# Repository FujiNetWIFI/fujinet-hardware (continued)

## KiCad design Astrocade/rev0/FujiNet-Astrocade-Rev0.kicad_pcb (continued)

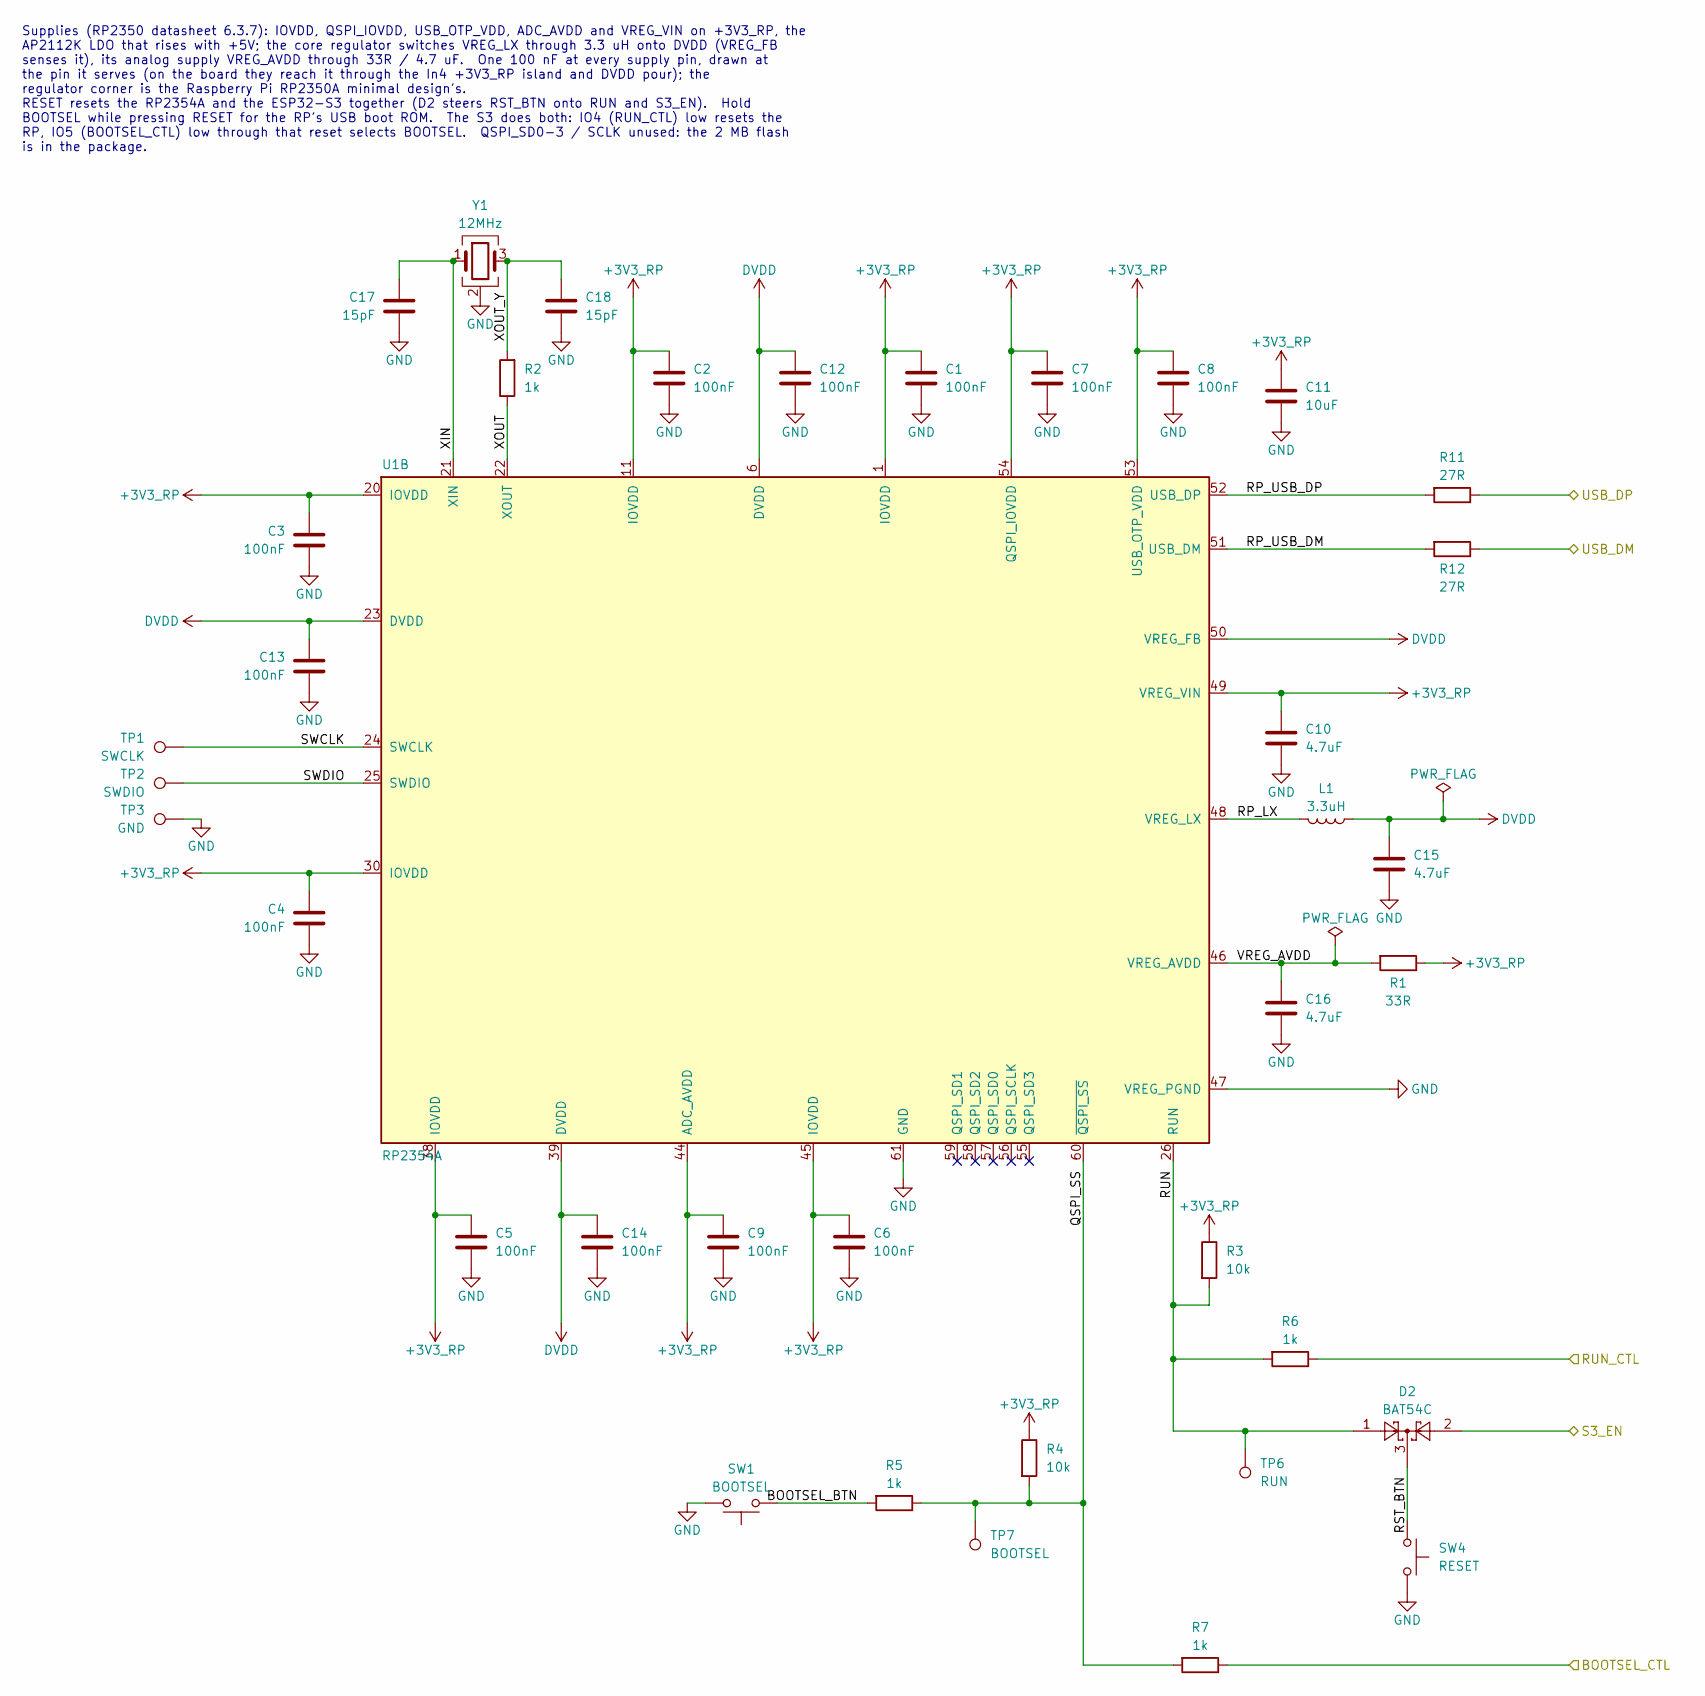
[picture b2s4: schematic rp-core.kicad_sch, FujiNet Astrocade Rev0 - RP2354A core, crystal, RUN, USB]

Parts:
C1, C2, C3, C4, C5, C6, C7, C9, C12, C13, C14: 100nF; C_0603_1608Metric; MPN CC0603KRX7R9BB104; LCSC C14663
C8: 100nF; RPI_C0402; MPN CL05B104KO5NNNC; LCSC C1525
C10, C15: 4.7uF; RPI_C0402_wide; MPN CL05A475MP5NRNC; LCSC C23733
C11: 10uF; C_0603_1608Metric; MPN CL10A106KP8NNNC; LCSC C19702
C16: 4.7uF; RPI_C0402; MPN CL05A475MP5NRNC; LCSC C23733
C17, C18: 15pF; C_0603_1608Metric; MPN CL10C150JB8NNNC; LCSC C1644
D2: BAT54C; SOT-23; MPN BAT54C,215; LCSC C37704
L1: 3.3uH; RPI_L_AOTA-B201610S3R3; MPN AOTA-B201610S3R3-101-T; LCSC C42411119
R1: 33R; RPI_R0402; MPN 0402WGF330JTCE; LCSC C25105
R2, R5, R6, R7: 1k; R_0603_1608Metric; MPN 0603WAF1001T5E; LCSC C21190
R3, R4: 10k; R_0603_1608Metric; MPN 0603WAF1002T5E; LCSC C25804
R11, R12: 27R; RPI_R0402; MPN 0402WGF270JTCE; LCSC C25100
SW1: BOOTSEL; SW_SPST_TL3342; MPN SKQGABE010; LCSC C115351
SW4: RESET; SW_SPST_TL3342; MPN SKQGABE010; LCSC C115351
TP1: SWCLK; TestPoint_Pad_D1.5mm
TP2: SWDIO; TestPoint_Pad_D1.5mm
TP3: GND; TestPoint_Pad_D1.5mm
TP6: RUN; TestPoint_Pad_D1.5mm
TP7: BOOTSEL; TestPoint_Pad_D1.5mm
U1: RP2354A; RPI_RP2350A_QFN60; MPN RP2354A; LCSC C41378174
Y1: 12MHz; Crystal_SMD_3225-4Pin_3.2x2.5mm; MPN ABM8-272-T3; LCSC C20625731

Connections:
+3V3_RP: C1.1, C2.1, C3.1, C4.1, C5.1, C6.1, C7.1, C8.1, C9.1, C10.1, C11.1, R1.1, R3.1, R4.1, U1.1 (IOVDD), U1.11 (IOVDD), U1.20 (IOVDD), U1.30 (IOVDD), U1.38 (IOVDD), U1.44 (ADC_AVDD), U1.45 (IOVDD), U1.49 (VREG_VIN), U1.53 (USB_OTP_VDD), U1.54 (QSPI_IOVDD); also elsewhere on the board
/BOOTSEL_CTL: R7.1; also elsewhere on the board
/RUN_CTL: R6.1; also elsewhere on the board
/S3_EN: D2.2; also elsewhere on the board
/USB_DM: R12.1; also elsewhere on the board
/USB_DP: R11.1; also elsewhere on the board
/rp-core/BOOTSEL_BTN: R5.2, SW1.1
/rp-core/QSPI_SS: R4.2, R5.1, R7.2, TP7.1, U1.60 (~QSPI_SS)
/rp-core/RP_LX: L1.2, U1.48 (VREG_LX)
/rp-core/RP_USB_DM: R12.2, U1.51 (USB_DM)
/rp-core/RP_USB_DP: R11.2, U1.52 (USB_DP)
/rp-core/RST_BTN: D2.3, SW4.1
/rp-core/RUN: D2.1, R3.2, R6.2, TP6.1, U1.26 (RUN)
/rp-core/SWCLK: TP1.1, U1.24 (SWCLK)
/rp-core/SWDIO: TP2.1, U1.25 (SWDIO)
/rp-core/VREG_AVDD: C16.1, R1.2, U1.46 (VREG_AVDD)
/rp-core/XIN: C17.1, U1.21 (XIN), Y1.1
/rp-core/XOUT: R2.1, U1.22 (XOUT)
/rp-core/XOUT_Y: C18.1, R2.2, Y1.3
DVDD: C12.1, C13.1, C14.1, C15.1, L1.1, U1.6 (DVDD), U1.23 (DVDD), U1.39 (DVDD), U1.50 (VREG_FB)
GND: C1.2, C2.2, C3.2, C4.2, C5.2, C6.2, C7.2, C8.2, C9.2, C10.2, C11.2, C12.2, C13.2, C14.2, C15.2, C16.2, C17.2, C18.2, SW1.2, SW4.2, TP3.1, U1.47 (VREG_PGND), U1.61 (GND), Y1.2 (G), Y1.4 (G); also elsewhere on the board

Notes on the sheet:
Supplies (RP2350 datasheet 6.3.7): IOVDD, QSPI_IOVDD, USB_OTP_VDD, ADC_AVDD and VREG_VIN on +3V3_RP, the AP2112K LDO that rises with +5V; the core regulator switches VREG_LX through 3.3 uH onto DVDD (VREG_FB senses it), its analog supply VREG_AVDD through 33R / 4.7 uF. One 100 nF at every supply pi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

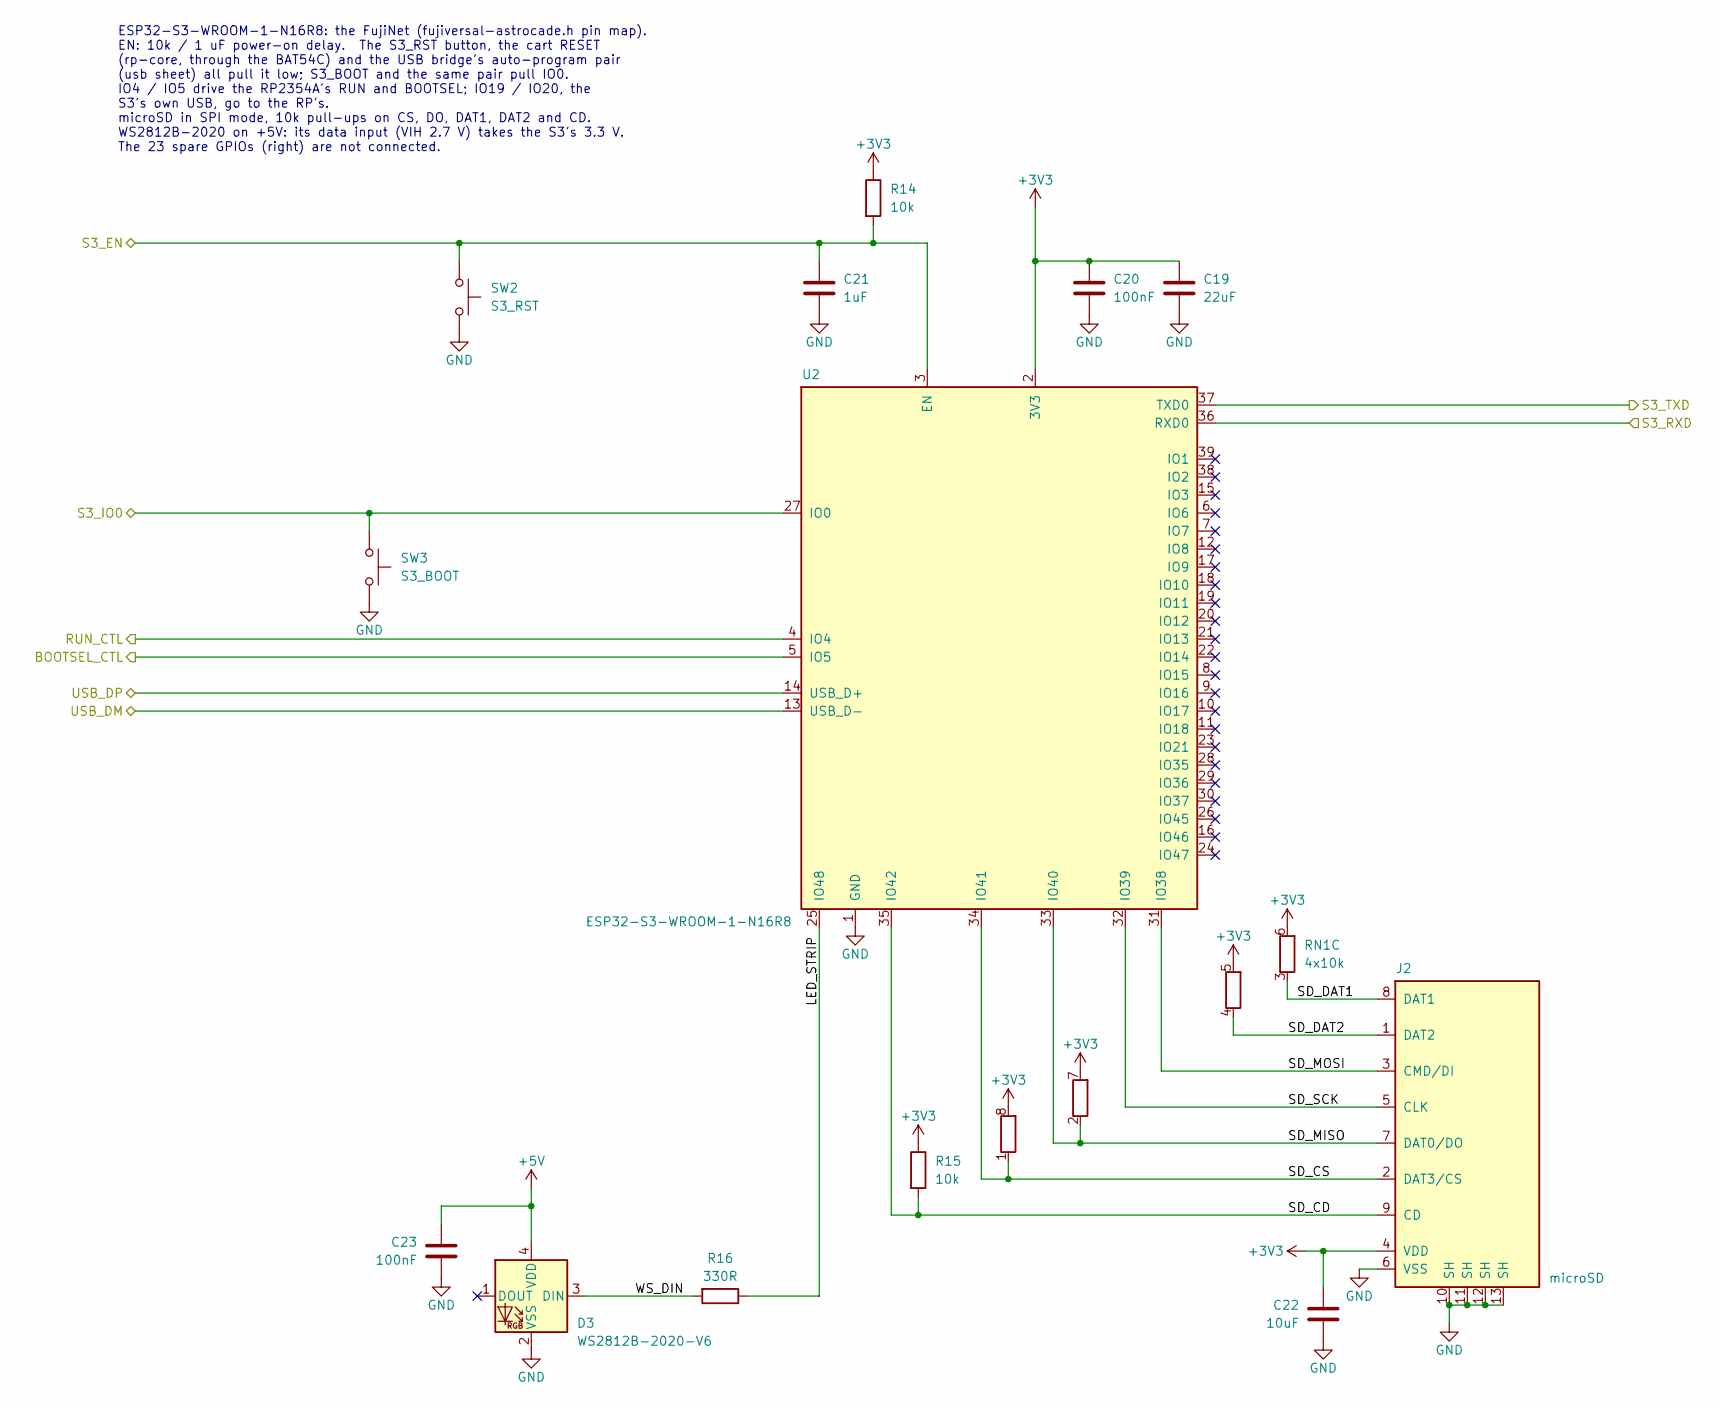
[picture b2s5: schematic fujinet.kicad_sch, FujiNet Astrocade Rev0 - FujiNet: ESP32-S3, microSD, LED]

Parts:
C19: 22uF; C_0805_2012Metric; MPN CL21A226MAQNNNE; LCSC C45783
C20, C23: 100nF; C_0603_1608Metric; MPN CC0603KRX7R9BB104; LCSC C14663
C21: 1uF; C_0603_1608Metric; MPN CL10A105KB8NNNC; LCSC C15849
C22: 10uF; C_0603_1608Metric; MPN CL10A106KP8NNNC; LCSC C19702
D3: WS2812B-2020-V6; LED_WS2812B-2020_PLCC4_2.0x2.0mm; MPN WS2812B-2020-V6; LCSC C52917434
J2: microSD; TF-SMD_TF-015; MPN TF-015; LCSC C113206
R14, R15: 10k; R_0603_1608Metric; MPN 0603WAF1002T5E; LCSC C25804
R16: 330R; R_0603_1608Metric; MPN 0603WAF3300T5E; LCSC C23138
RN1: 4x10k; R_Array_Convex_4x0603; MPN 4D03WGJ0103T5E; LCSC C29718
SW2: S3_RST; SW_SPST_TL3342; MPN TL3342F160QG; LCSC C2886898
SW3: S3_BOOT; SW_SPST_TL3342; MPN TL3342F160QG; LCSC C2886898
U2: ESP32-S3-WROOM-1-N16R8; ESP32-S3-WROOM-1; MPN ESP32-S3-WROOM-1-N16R8; LCSC C2913202

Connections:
+3V3: C19.1, C20.1, C22.1, J2.4 (VDD), R14.1, R15.1, RN1.5 (R4.2), RN1.6 (R3.2), RN1.7 (R2.2), RN1.8 (R1.2), U2.2 (3V3); also elsewhere on the board
+5V: C23.1, D3.4 (VDD); also elsewhere on the board
/BOOTSEL_CTL: U2.5 (IO5); also elsewhere on the board
/RUN_CTL: U2.4 (IO4); also elsewhere on the board
/S3_EN: C21.1, R14.2, SW2.1, U2.3 (EN); also elsewhere on the board
/S3_IO0: SW3.1, U2.27 (IO0); also elsewhere on the board
/S3_RXD: U2.36 (RXD0); also elsewhere on the board
/S3_TXD: U2.37 (TXD0); also elsewhere on the board
/USB_DM: U2.13 (USB_D-); also elsewhere on the board
/USB_DP: U2.14 (USB_D+); also elsewhere on the board
/fujinet/LED_STRIP: R16.1, U2.25 (IO48)
/fujinet/SD_CD: J2.9 (CD), R15.2, U2.35 (IO42)
/fujinet/SD_CS: J2.2 (DAT3/CS), RN1.1 (R1.1), U2.34 (IO41)
/fujinet/SD_DAT1: J2.8 (DAT1), RN1.3 (R3.1)
/fujinet/SD_DAT2: J2.1 (DAT2), RN1.4 (R4.1)
/fujinet/SD_MISO: J2.7 (DAT0/DO), RN1.2 (R2.1), U2.33 (IO40)
/fujinet/SD_MOSI: J2.3 (CMD/DI), U2.31 (IO38)
/fujinet/SD_SCK: J2.5 (CLK), U2.32 (IO39)
/fujinet/WS_DIN: D3.3 (DIN), R16.2
GND: C19.2, C20.2, C21.2, C22.2, C23.2, D3.2 (VSS), J2.6 (VSS), J2.10 (SH), J2.11 (SH), J2.12 (SH), J2.13 (SH), SW2.2, SW3.2, U2.1 (GND), U2.40 (GND), U2.41 (GND); also elsewhere on the board

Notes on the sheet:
ESP32-S3-WROOM-1-N16R8: the FujiNet (fujiversal-astrocade.h pin map). EN: 10k / 1 uF power-on delay. The S3_RST button, the cart RESET (rp-core, through the BAT54C) and the USB bridge's auto-program pair (usb sheet) all pull it low; S3_BOOT and the same pair pull IO0. IO4 / IO5 drive the RP2354A's 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

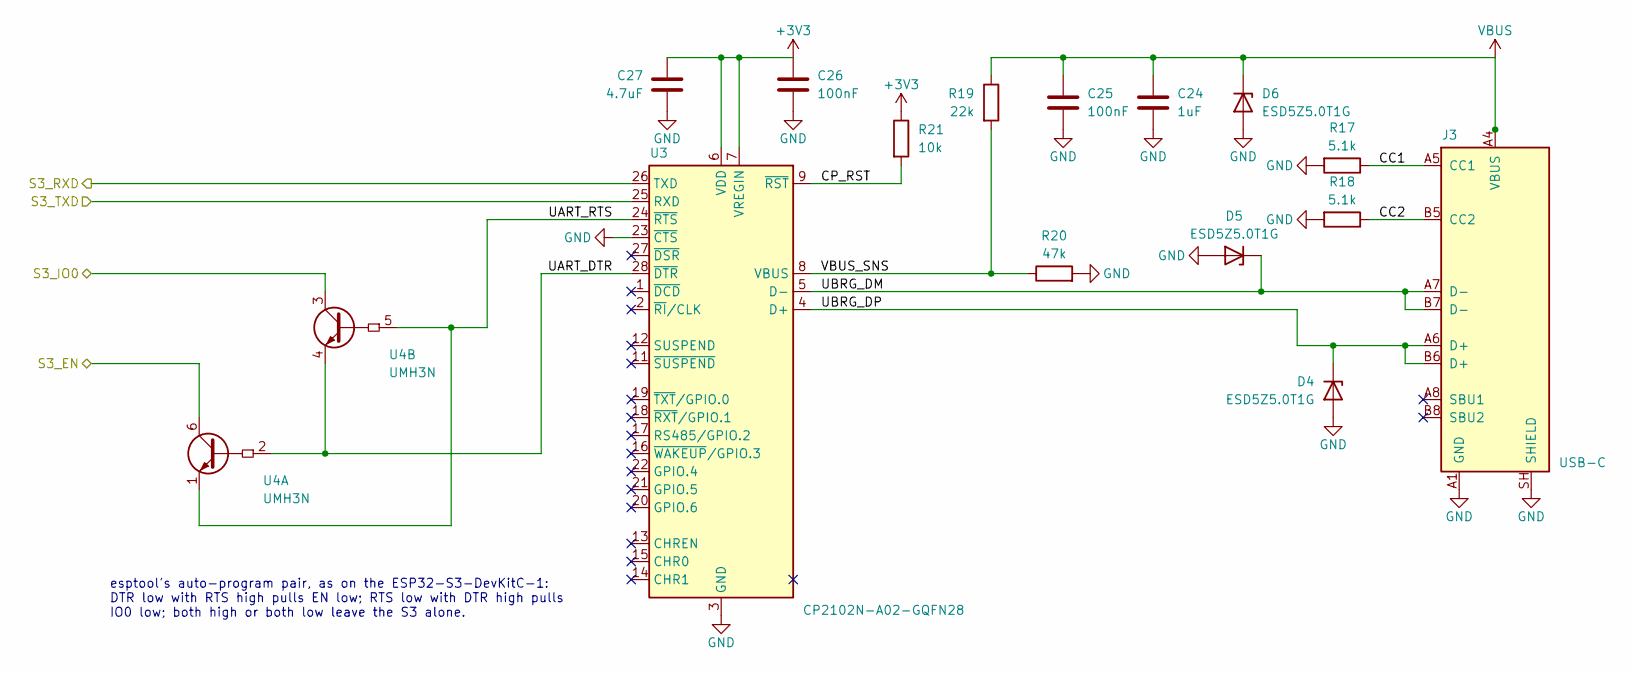
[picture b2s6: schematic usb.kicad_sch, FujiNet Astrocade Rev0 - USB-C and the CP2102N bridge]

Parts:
C24: 1uF; C_0603_1608Metric; MPN CL10A105KB8NNNC; LCSC C15849
C25, C26: 100nF; C_0603_1608Metric; MPN CC0603KRX7R9BB104; LCSC C14663
C27: 4.7uF; C_0603_1608Metric; MPN CL10A475KO8NNNC; LCSC C19666
D4, D5, D6: ESD5Z5.0T1G; D_SOD-523; MPN ESD5Z5.0T1G; LCSC C82044
J3: USB-C; USB_C_Receptacle_HRO_TYPE-C-31-M-12; MPN TYPE-C-31-M-12; LCSC C165948
R17, R18: 5.1k; R_0603_1608Metric; MPN 0603WAF5101T5E; LCSC C23186
R19: 22k; R_0603_1608Metric; MPN 0603WAF2202T5E; LCSC C31850
R20: 47k; R_0603_1608Metric; MPN 0603WAF4702T5E; LCSC C25819
R21: 10k; R_0603_1608Metric; MPN 0603WAF1002T5E; LCSC C25804
U3: CP2102N-A02-GQFN28; QFN-28-1EP_5x5mm_P0.5mm_EP3.35x3.35mm; MPN CP2102N-A02-GQFN28R; LCSC C964632
U4: UMH3N; SOT-363_SC-70-6; MPN UMH3N; LCSC C62892

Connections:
+3V3: C26.1, C27.1, R21.1, U3.6 (VDD), U3.7 (VREGIN); also elsewhere on the board
/S3_EN: U4.6 (C1); also elsewhere on the board
/S3_IO0: U4.3 (C2); also elsewhere on the board
/S3_RXD: U3.26 (TXD); also elsewhere on the board
/S3_TXD: U3.25 (RXD); also elsewhere on the board
/usb/CC1: J3.A5 (CC1), R17.1
/usb/CC2: J3.B5 (CC2), R18.1
/usb/CP_RST: R21.2, U3.9 (~RST)
/usb/UART_DTR: U3.28 (~DTR), U4.2 (B1), U4.4 (E2)
/usb/UART_RTS: U3.24 (~RTS), U4.1 (E1), U4.5 (B2)
/usb/UBRG_DM: D5.1 (K), J3.A7 (D-), J3.B7 (D-), U3.5 (D-)
/usb/UBRG_DP: D4.1 (K), J3.A6 (D+), J3.B6 (D+), U3.4 (D+)
/usb/VBUS_SNS: R19.2, R20.1, U3.8 (VBUS)
GND: C24.2, C25.2, C26.2, C27.2, D4.2 (A), D5.2 (A), D6.2 (A), J3.A1 (GND), J3.A12 (GND), J3.B1 (GND), J3.B12 (GND), J3.SH (SHIELD), R17.2, R18.2, R20.2, U3.3 (GND), U3.23 (~CTS), U3.29 (GND); also elsewhere on the board
VBUS: C24.1, C25.1, D6.1 (K), J3.A4 (VBUS), J3.A9 (VBUS), J3.B4 (VBUS), J3.B9 (VBUS), R19.1; also elsewhere on the board

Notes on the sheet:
esptool's auto-program pair, as on the ESP32-S3-DevKitC-1: DTR low with RTS high pulls EN low; RTS low with DTR high pulls IO0 low; both high or both low leave the S3 alone.

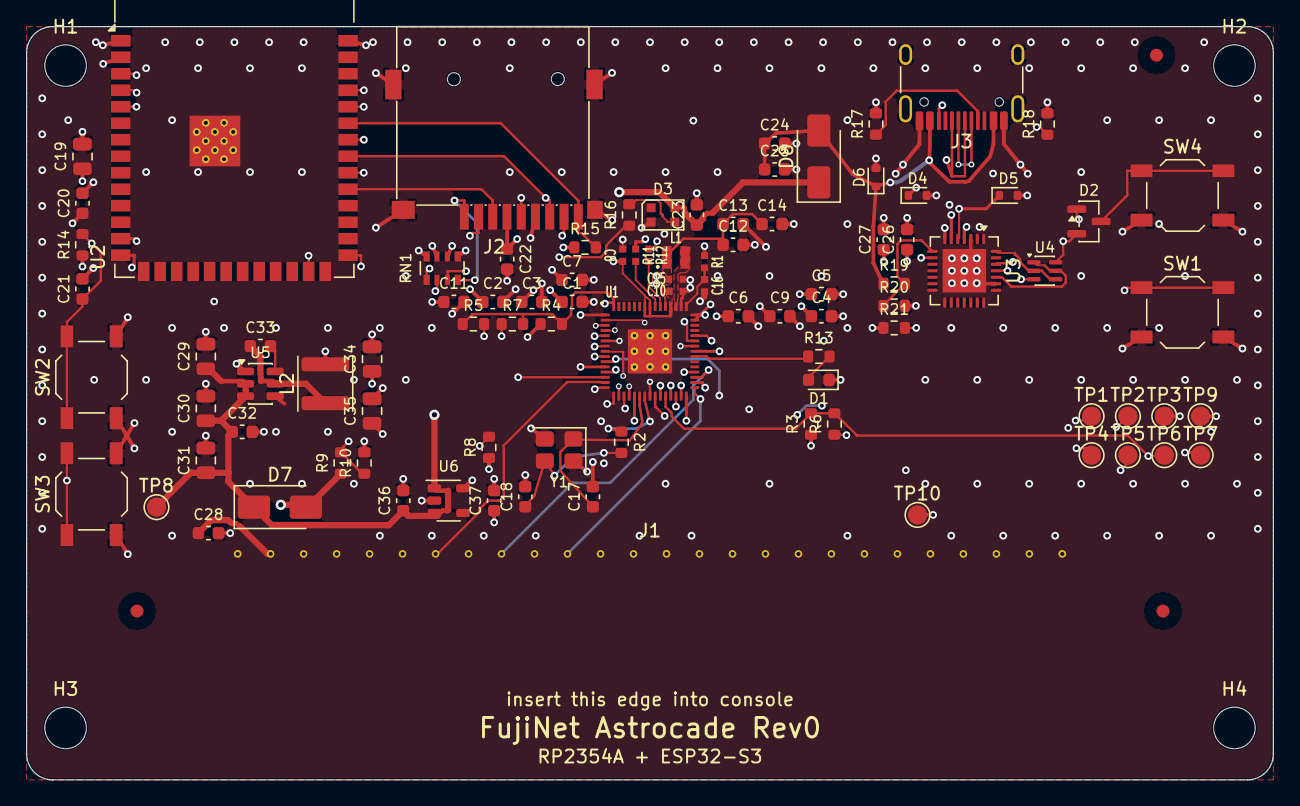
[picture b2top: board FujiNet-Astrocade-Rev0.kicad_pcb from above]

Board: 6 copper layers, 96.0 x 58.0 mm, 100 parts (0 on the bottom side), 74 nets.

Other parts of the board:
FID1, FID2, FID3: Fiducial_1mm_Mask2mm
H1, H2, H3, H4: M3; MountingHole_3.2mm_NPTH

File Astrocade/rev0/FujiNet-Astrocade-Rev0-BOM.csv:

"Refs","Value","Footprint","MPN","LCSC","Description","DNP"
"C1,C2,C3,C4,C5,C6,C7,C9,C12,C13,C14,C20,C23,C25,C26,C28,C32,C33","100nF","C_0603_1608Metric","CC0603KRX7R9BB104","C14663","IOVDD decoupling",""
"C8","100nF","RPI_C0402","CL05B104KO5NNNC","C1525","USB_OTP_VDD + QSPI_IOVDD decoupling",""
"C10,C15","4.7uF","RPI_C0402_wide","CL05A475MP5NRNC","C23733","VREG_VIN bulk",""
"C11,C22","10uF","C_0603_1608Metric","CL10A106KP8NNNC","C19702","RP 3V3 bulk",""
"C16","4.7uF","RPI_C0402","CL05A475MP5NRNC","C23733","VREG_AVDD filter",""
"C17,C18","15pF","C_0603_1608Metric","CL10C150JB8NNNC","C1644","crystal load",""
"C19,C29,C30,C31,C34,C35","22uF","C_0805_2012Metric","CL21A226MAQNNNE","C45783","S3 bulk (WiFi TX bursts)",""
"C21,C24,C36,C37","1uF","C_0603_1608Metric","CL10A105KB8NNNC","C15849","EN power-on delay",""
"C27","4.7uF","C_0603_1608Metric","CL10A475KO8NNNC","C19666","CP2102N VDD bulk",""
"D1","green","LED_0603_1608Metric","KT-0603G","C12624","RP activity LED",""
"D2","BAT54C","SOT-23","BAT54C,215","C37704","RESET steering, common cathode",""
"D3","WS2812B-2020-V6","LED_WS2812B-2020_PLCC4_2.0x2.0mm","WS2812B-2020-V6","C52917434","status LED on +5V (datasheet VDD 3.7-5.3 V; VIH 2.7 V takes 3.3 V data)",""
"D4,D5,D6","ESD5Z5.0T1G","D_SOD-523","ESD5Z5.0T1G","C82044","ESD",""
"D7,D8","SS34","D_SMA","SS34","C8678","console 5V OR-ing",""
"J2","microSD","TF-SMD_TF-015","TF-015","C113206","microSD push-push, SPI mode",""
"J3","USB-C","USB_C_Receptacle_HRO_TYPE-C-31-M-12","TYPE-C-31-M-12","C165948","power + S3 programming",""
"L1","3.3uH","RPI_L_AOTA-B201610S3R3","AOTA-B201610S3R3-101-T","C42411119","RP2350 core SMPS inductor",""
"L2","6.8uH","L_Sunlord_SWPA4030S","SWPA4030S6R8MT","C62684","buck inductor",""
"R1","33R","RPI_R0402","0402WGF330JTCE","C25105","VREG_AVDD filter",""
"R2,R5,R6,R7","1k","R_0603_1608Metric","0603WAF1001T5E","C21190","crystal drive limit",""
"R3,R4,R8,R9,R14,R15,R21","10k","R_0603_1608Metric","0603WAF1002T5E","C25804","RUN pull-up",""
"R10","15k","R_0603_1608Metric","0603WAF1502T5E","C22809","console 5V sense -> 3.0V (6 kOhm: beats RP2350-E9)",""
"R11,R12","27R","RPI_R0402","0402WGF270JTCE","C25100","USB series",""
"R13,R16","330R","R_0603_1608Metric","0603WAF3300T5E","C23138","LED series (KT-0603G VF ~2.6-2.85 V: 1.5-2 mA from 3.3 V)",""
"R17,R18","5.1k","R_0603_1608Metric","0603WAF5101T5E","C23186","UFP Rd",""
"R19","22k","R_0603_1608Metric","0603WAF2202T5E","C31850","VBUS sense divider",""
"R20","47k","R_0603_1608Metric","0603WAF4702T5E","C25819","VBUS sense divider",""
"RN1","4x10k","R_Array_Convex_4x0603","4D03WGJ0103T5E","C29718","SD pull-ups",""
"SW1","BOOTSEL","SW_SPST_TL3342","SKQGABE010","C115351","RP2354 BOOTSEL (hold while pressing RESET)",""
"SW2","S3_RST","SW_SPST_TL3342","SKQGABE010","C115351","ESP32-S3 EN",""
"SW3","S3_BOOT","SW_SPST_TL3342","SKQGABE010","C115351","ESP32-S3 BOOT (IO0)",""
"SW4","RESET","SW_SPST_TL3342","SKQGABE010","C115351","cart RESET: RP RUN + S3 EN via BAT54C",""
"U1","RP2354A","RPI_RP2350A_QFN60","RP2354A","C41378174","RP2350A + 2MB flash in package; cart bus server",""
"U2","ESP32-S3-WROOM-1-N16R8","ESP32-S3-WROOM-1","ESP32-S3-WROOM-1-N16R8","C2913202","FujiNet core (fujiversal-astrocade)",""
"U3","CP2102N-A02-GQFN28","QFN-28-1EP_5x5mm_P0.5mm_EP3.35x3.35mm","CP2102N-A02-GQFN28R","C964632","USB-UART for S3 flashing/console (self-powered)",""
"U4","UMH3N","SOT-363_SC-70-6","UMH3N","C62892","esptool auto-program (DevKitC-1 style)",""
"U5","AP63203WU","TSOT-23-6","AP63203WU-7","C780769","3.3V 2A buck",""
"U6","AP2112K-3.3","SOT-23-5","AP2112K-3.3TRG1","C51118","RP2354A 3.3V LDO (IOVDD, VREG_VIN, VREG_AVDD), fast start",""
"Y1","12MHz","Crystal_SMD_3225-4Pin_3.2x2.5mm","ABM8-272-T3","C20625731","",""

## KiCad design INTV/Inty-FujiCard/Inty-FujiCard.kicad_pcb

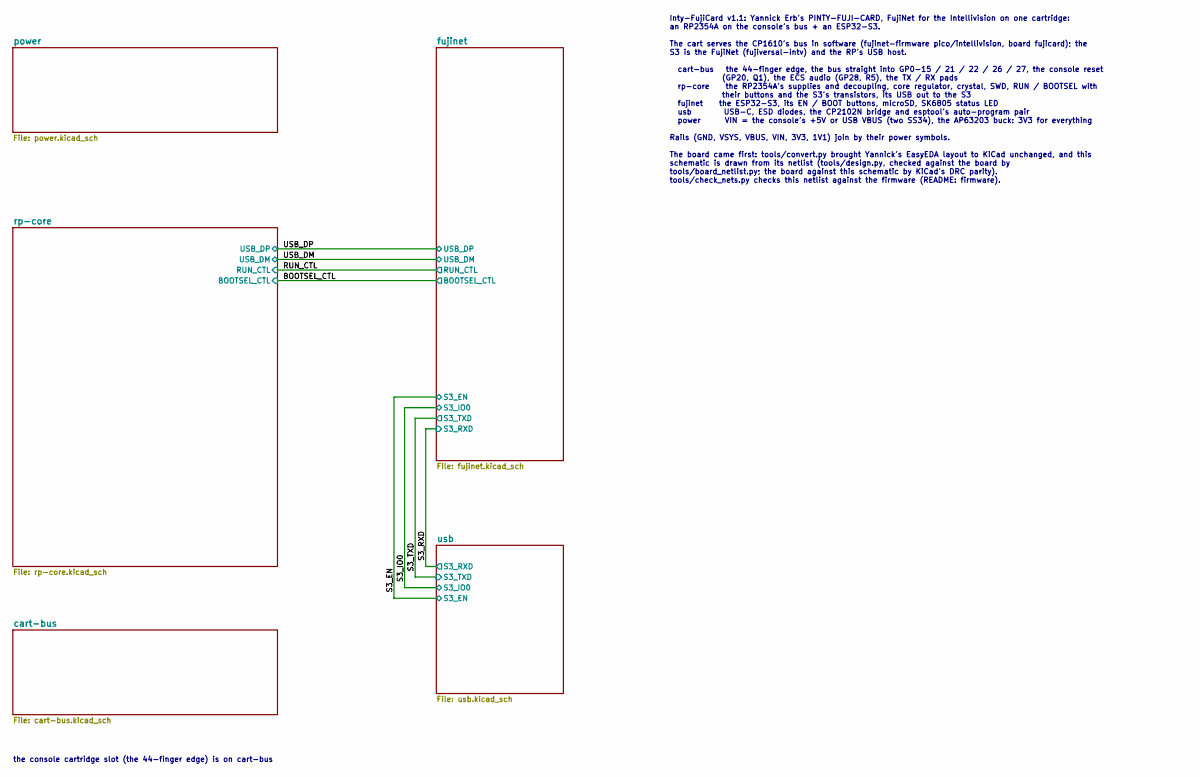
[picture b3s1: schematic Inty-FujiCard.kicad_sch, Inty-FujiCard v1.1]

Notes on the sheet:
the console cartridge slot (the 44-finger edge) is on cart-bus
Inty-FujiCard v1.1: Yannick Erb's PINTY-FUJI-CARD, FujiNet for the Intellivision on one cartridge: an RP2354A on the console's bus + an ESP32-S3. The cart serves the CP1610's bus in software (fujinet-firmware pico/intellivision, board fujicard); the S3 is the FujiNet (fujiversal-intv) and the RP's 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

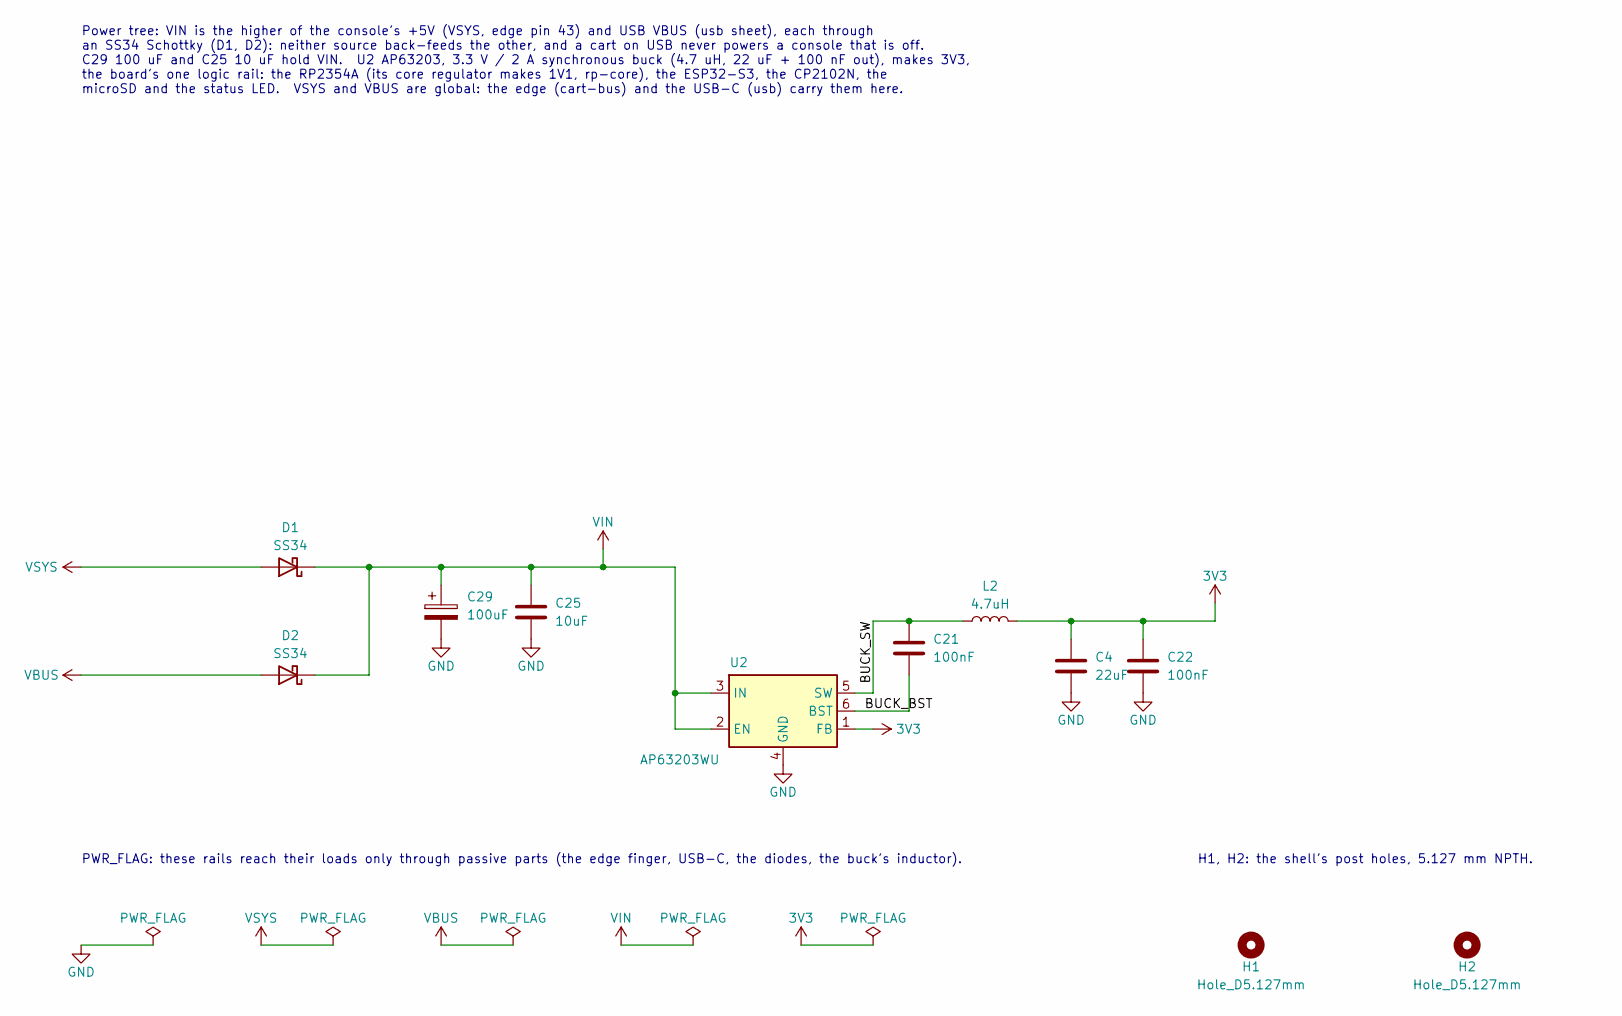
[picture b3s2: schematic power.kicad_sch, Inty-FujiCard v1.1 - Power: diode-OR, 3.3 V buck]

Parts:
C4: 22uF; C0603; MPN CL10A226MQ8NRNC; LCSC C59461
C21, C22: 100nF; C0402; MPN CL05B104KO5NNNC; LCSC C1525
C25: 10uF; C0603; MPN CL10A106KP8NNNC; LCSC C19702
C29: 100uF; CAP-SMD_BD5.0-L5.3-W5.3-RD; MPN VE-101M1ATR-0505; LCSC C134722
D1, D2: SS34; SMA_L4.3-W2.6-LS5.2-RD; MPN SS34; LCSC C8678
H1, H2: Hole_D5.127mm; Hole_D5.127mm_NPTH
L2: 4.7uH; IND-SMD_L3.0-W3.0-1; MPN YNR3015-4R7M; LCSC C340361
U2: AP63203WU; TSOT-26_L2.9-W1.6-P0.95-LS2.8-BL; MPN AP63203WU-7; LCSC C780769

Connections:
3V3: C4.2, C22.2, L2.2, U2.1 (FB); also elsewhere on the board
/power/BUCK_BST: C21.2, U2.6 (BST)
/power/BUCK_SW: C21.1, L2.1, U2.5 (SW)
GND: C4.1, C22.1, C25.1, C29.2, U2.4 (GND); also elsewhere on the board
VBUS: D2.2 (A); also elsewhere on the board
VIN: C25.2, C29.1, D1.1 (K), D2.1 (K), U2.2 (EN), U2.3 (IN)
VSYS: D1.2 (A); also elsewhere on the board

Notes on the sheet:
PWR_FLAG: these rails reach their loads only through passive parts (the edge finger, USB-C, the diodes, the buck's inductor).
H1, H2: the shell's post holes, 5.127 mm NPTH.
Power tree: VIN is the higher of the console's +5V (VSYS, edge pin 43) and USB VBUS (usb sheet), each through an SS34 Schottky (D1, D2): neither source back-feeds the other, and a cart on USB never powers a console that is off. C29 100 uF and C25 10 uF hold VIN. U2 AP63203, 3.3 V / 2 A synchronous 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

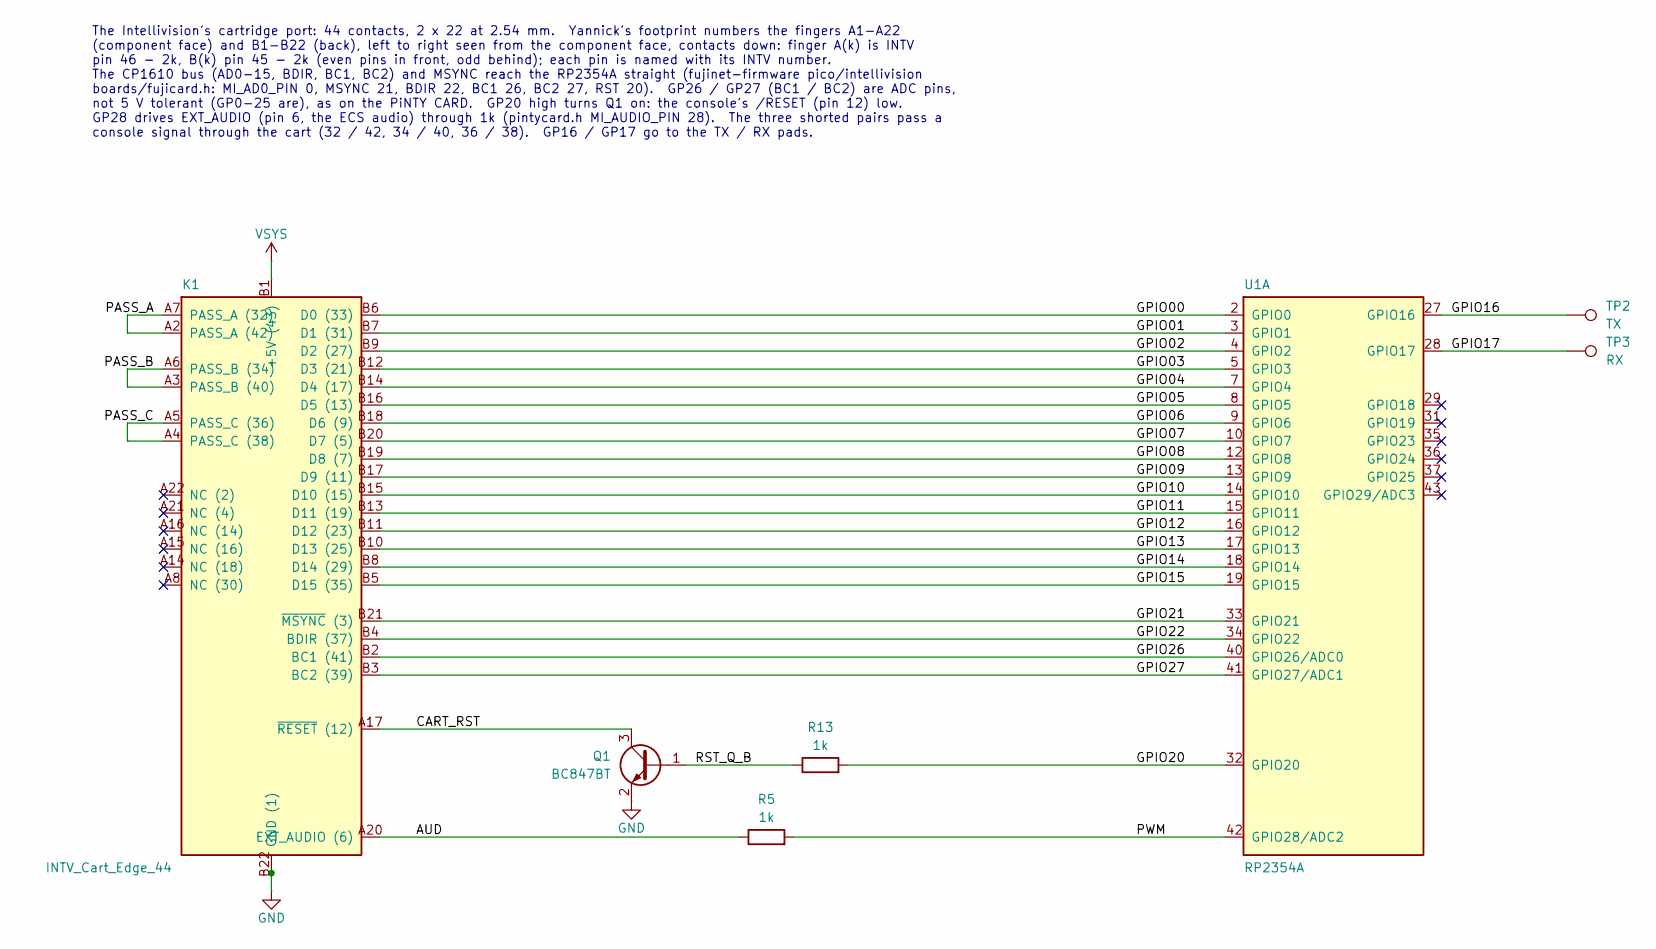
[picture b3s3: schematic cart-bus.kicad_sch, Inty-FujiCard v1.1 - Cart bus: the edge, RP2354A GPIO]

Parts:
K1: INTV_Cart_Edge_44; PCB_EDGE_CONNECTOR_22X2
Q1: BC847BT; SOT-523-3_L1.6-W0.8-P1.00-LS1.6-BR; MPN BC847BT; LCSC C5186022
R5, R13: 1k; R0402; MPN 0402WGF1001TCE; LCSC C11702
TP2: TX; TESTPOINT_PAD_D1.5MM
TP3: RX; TESTPOINT_PAD_D1.5MM
U1: RP2354A; QFN-60_L7.0-W7.0-P0.40-TL-EP3.4; MPN RP2354A; LCSC C41378174

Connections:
/cart-bus/AUD: K1.A20 (EXT_AUDIO (6)), R5.1
/cart-bus/CART_RST: K1.A17 (~RESET (12)), Q1.3 (C)
/cart-bus/GPIO00: K1.B6 (D0 (33)), U1.2 (GPIO0)
/cart-bus/GPIO01: K1.B7 (D1 (31)), U1.3 (GPIO1)
/cart-bus/GPIO02: K1.B9 (D2 (27)), U1.4 (GPIO2)
/cart-bus/GPIO03: K1.B12 (D3 (21)), U1.5 (GPIO3)
/cart-bus/GPIO04: K1.B14 (D4 (17)), U1.7 (GPIO4)
/cart-bus/GPIO05: K1.B16 (D5 (13)), U1.8 (GPIO5)
/cart-bus/GPIO06: K1.B18 (D6 (9)), U1.9 (GPIO6)
/cart-bus/GPIO07: K1.B20 (D7 (5)), U1.10 (GPIO7)
/cart-bus/GPIO08: K1.B19 (D8 (7)), U1.12 (GPIO8)
/cart-bus/GPIO09: K1.B17 (D9 (11)), U1.13 (GPIO9)
/cart-bus/GPIO10: K1.B15 (D10 (15)), U1.14 (GPIO10)
/cart-bus/GPIO11: K1.B13 (D11 (19)), U1.15 (GPIO11)
/cart-bus/GPIO12: K1.B11 (D12 (23)), U1.16 (GPIO12)
/cart-bus/GPIO13: K1.B10 (D13 (25)), U1.17 (GPIO13)
/cart-bus/GPIO14: K1.B8 (D14 (29)), U1.18 (GPIO14)
/cart-bus/GPIO15: K1.B5 (D15 (35)), U1.19 (GPIO15)
/cart-bus/GPIO16: TP2.1, U1.27 (GPIO16)
/cart-bus/GPIO17: TP3.1, U1.28 (GPIO17)
/cart-bus/GPIO20: R13.2, U1.32 (GPIO20)
/cart-bus/GPIO21: K1.B21 (~MSYNC (3)), U1.33 (GPIO21)
/cart-bus/GPIO22: K1.B4 (BDIR (37)), U1.34 (GPIO22)
/cart-bus/GPIO26: K1.B2 (BC1 (41)), U1.40 (GPIO26/ADC0)
/cart-bus/GPIO27: K1.B3 (BC2 (39)), U1.41 (GPIO27/ADC1)
/cart-bus/PASS_A: K1.A2 (PASS_A (42)), K1.A7 (PASS_A (32))
/cart-bus/PASS_B: K1.A3 (PASS_B (40)), K1.A6 (PASS_B (34))
/cart-bus/PASS_C: K1.A4 (PASS_C (38)), K1.A5 (PASS_C (36))
/cart-bus/PWM: R5.2, U1.42 (GPIO28/ADC2)
/cart-bus/RST_Q_B: Q1.1 (B), R13.1
GND: K1.A1 (GND (44)), K1.A9 (GND (28)), K1.A10 (GND (26)), K1.A11 (GND (24)), K1.A12 (GND (22)), K1.A13 (GND (20)), K1.A18 (GND (10)), K1.A19 (GND (8)), K1.B22 (GND (1)), Q1.2 (E); also elsewhere on the board
VSYS: K1.B1 (+5V (43)); also elsewhere on the board

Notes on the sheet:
The Intellivision's cartridge port: 44 contacts, 2 x 22 at 2.54 mm. Yannick's footprint numbers the fingers A1-A22 (component face) and B1-B22 (back), left to right seen from the component face, contacts down: finger A(k) is INTV pin 46 - 2k, B(k) pin 45 - 2k (even pins in front, odd behind); each 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
